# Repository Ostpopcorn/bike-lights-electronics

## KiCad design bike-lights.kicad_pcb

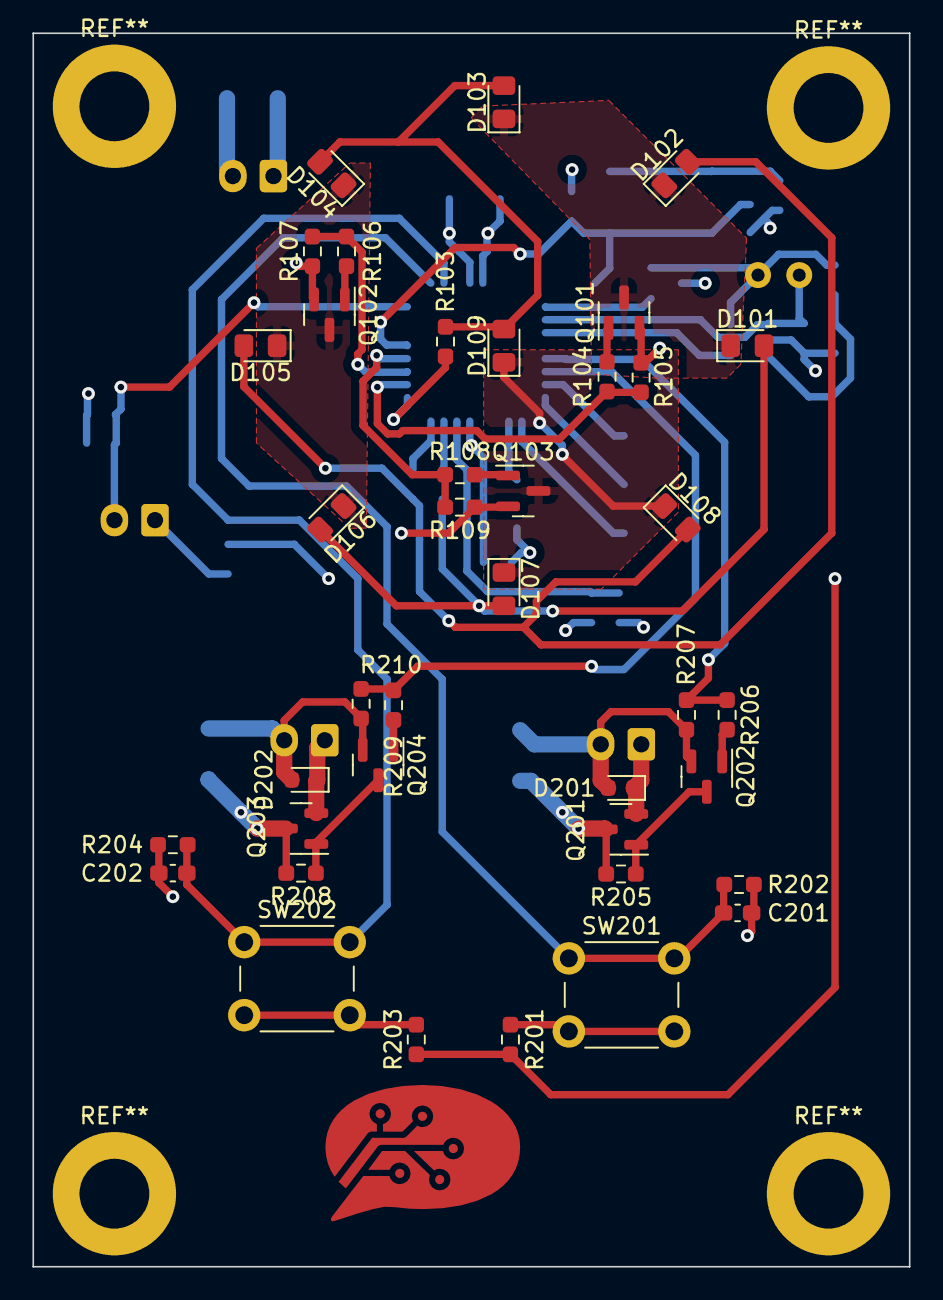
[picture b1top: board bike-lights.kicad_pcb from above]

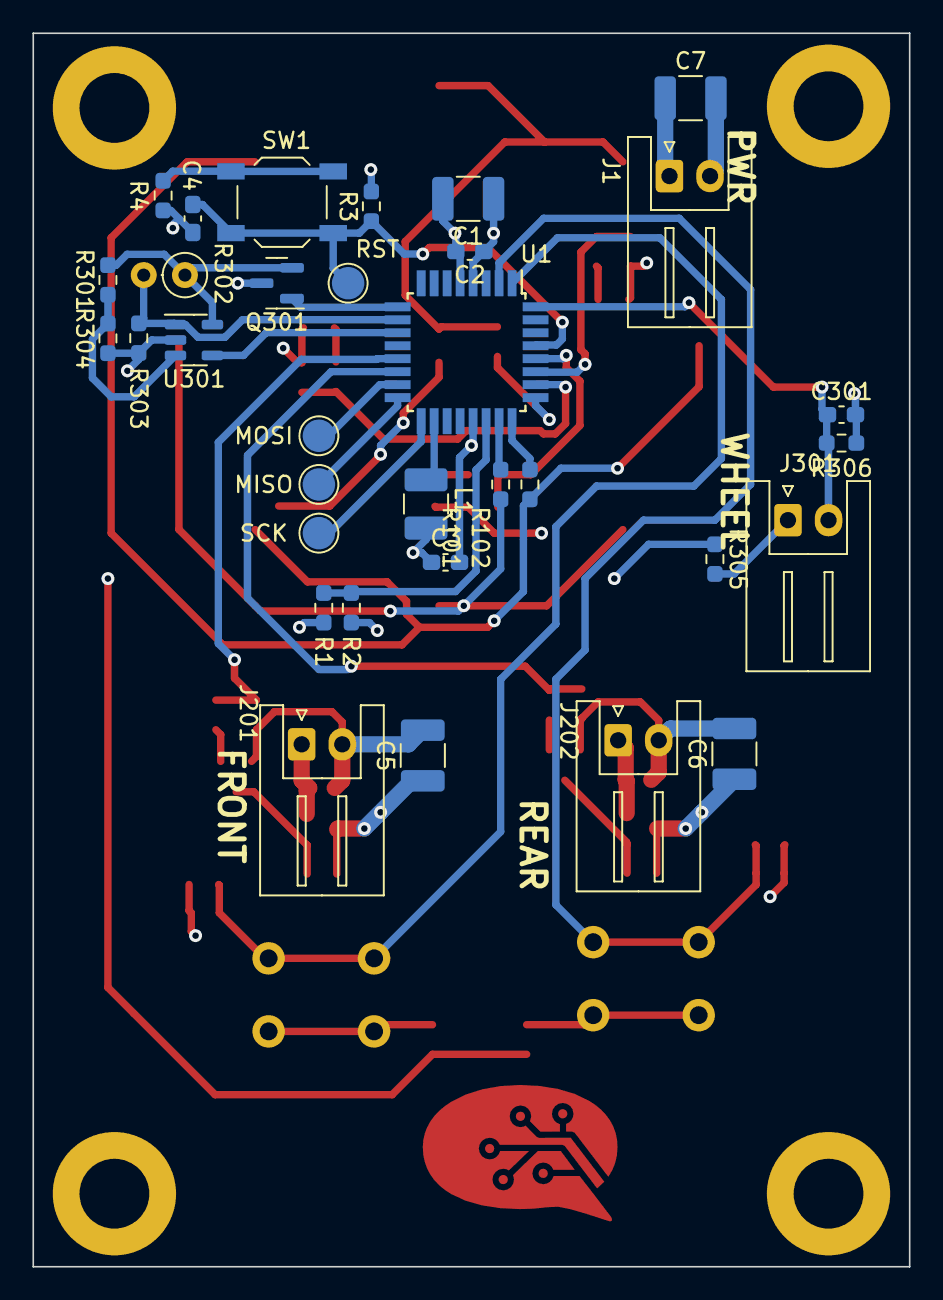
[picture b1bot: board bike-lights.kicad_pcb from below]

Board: 4 copper layers, 54.0 x 76.0 mm, 73 parts (33 on the bottom side), 44 nets.

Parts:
C1, C5, C6, C7: 10uF; C_1210_3225Metric_Pad1.33x2.70mm_HandSolder
C2, C3, C4, C201, C202, C301: 100nF; C_0603_1608Metric_Pad1.08x0.95mm_HandSolder
D101, D102, D103, D104, D105, D106, D107, D108, D109: LED_Small; LED_0805_2012Metric_Pad1.15x1.40mm_HandSolder
D201, D202: D; D_0603_1608Metric
J1: Conn_01x02_Female; JST_XH_S2B-XH-A_1x02_P2.50mm_Horizontal
J201, J202, J301: Conn_01x02_Male; JST_XH_S2B-XH-A_1x02_P2.50mm_Horizontal
L1: L; L_1210_3225Metric_Pad1.42x2.65mm_HandSolder
MISO: TestPoint_Pad_D2.0mm
MOSI: TestPoint_Pad_D2.0mm
Q101, Q102, Q103, Q202, Q204: BST82-1; SOT-23
Q201, Q203, Q301: A1SHB; SOT-23
R1, R2, R105, R107, R207, R210, R301, R304: 100k; R_0603_1608Metric_Pad0.98x0.95mm_HandSolder
R3, R109, R303: 10k; R_0603_1608Metric_Pad0.98x0.95mm_HandSolder
R4, R201, R203, R305: 10R; R_0603_1608Metric_Pad0.98x0.95mm_HandSolder
R101, R102, R103: R; R_0603_1608Metric_Pad0.98x0.95mm_HandSolder
R104, R106, R108, R206, R209: R100; R_0603_1608Metric_Pad0.98x0.95mm_HandSolder
R202, R204, R306: 10K; R_0603_1608Metric_Pad0.98x0.95mm_HandSolder
R205, R208: 1k; R_0603_1608Metric_Pad0.98x0.95mm_HandSolder
R302: R_Photo; R_Axial_DIN0207_L6.3mm_D2.5mm_P2.54mm_Vertical
RST: TestPoint_Pad_D2.0mm
SCK: TestPoint_Pad_D2.0mm
SW1: SW_Push; SW_SPST_TL3342
SW201, SW202: SW_Push; SW_PUSH_6mm_H5mm
U1: ATtiny48-A; TQFP-32_7x7mm_P0.8mm
U301: LM397; SOT-23-5
ost-bubble_12mm_Copper: G***; ost-bubble_12mm_Copper

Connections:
+3V3: C1.1, C2.1, C3.1, L1.1, Q301.3 (D), R3.2, R201.1, R203.1, R305.1, U1.4 (VCC)
/3V3PHOTO: Q301.2 (S), R301.2, R302.1, U301.5 (V+)
/BTN1: C201.1, R202.1, SW201.1, U1.1 (PD3)
/BTN2: C202.1, R204.1, SW202.1, U1.2 (PD4)
/ENABLEPHOTO: Q301.1 (G), U1.9 (PD5)
/LEDA1: R101.2, U1.23 (PC0)
/LEDA1INT: D101.2 (A), D106.2 (A), D107.2 (A), R101.1
/LEDA2: R102.2, U1.24 (PC1)
/LEDA2INT: D102.2 (A), D105.2 (A), D108.2 (A), R102.1
/LEDA3: R103.2, U1.25 (PC2)
/LEDA3INT: D103.2 (A), D104.2 (A), D109.2 (A), R103.1
/LEDC1: R104.2, R105.1, U1.26 (PC3)
/LEDC2: R106.2, R107.2, U1.27 (PC4)
/LEDC3: R108.1, R109.2, U1.28 (PC5)
/LIGHTF: R206.1, R207.2, U1.13 (PB1)
/LIGHTR: R209.1, R210.2, U1.14 (PB2)
/MISO: MISO.1, U1.16 (PB4)
/MOSI: MOSI.1, U1.15 (PB3)
/PHOTO: R302.2, R303.2, U1.10 (PD6), U301.1 (-)
/PHOTOCOMP: U1.11 (PD7), U301.4
/RESET: C4.1, R3.1, RST.1, SW1.1, U1.29 (~RESET/PC6)
/SCK: SCK.1, U1.17 (PB5)
/VSENSE: R1.1, R2.2, U1.22 (PA1)
/WHEEL: C301.1, J301.2, R306.1, U1.32 (PD2)
GND: C1.2, C2.2, C3.2, C4.2, C5.2, C6.2, C7.2, C201.2, C202.2, C301.2, D201.2 (A), D202.2 (A), J1.2, J201.2, J202.2, Q101.2 (S), Q102.2 (S), Q103.2 (S), Q202.2 (S), Q204.2 (S), R2.1, R4.2, R105.2, R107.1, R109.1, R202.2, R204.2, R207.1, R210.1, R303.1, R304.1, R306.2, U1.5 (GND), U1.21 (GND), U301.2 (V-)
unnamed: D101.1 (K), D102.1 (K), D103.1 (K), Q101.3 (D)
unnamed: D104.1 (K), D105.1 (K), D106.1 (K), Q102.3 (D)
unnamed: D107.1 (K), D108.1 (K), D109.1 (K), Q103.3 (D)
unnamed: D201.1 (K), J201.1, Q201.2 (S)
unnamed: D202.1 (K), J202.1, Q203.2 (S)
unnamed: J301.1, R305.2
unnamed: L1.2, U1.18 (AVCC)
unnamed: Q101.1 (G), R104.1
unnamed: Q102.1 (G), R106.1
unnamed: Q103.1 (G), R108.2
unnamed: Q201.1 (G), Q202.3 (D), R205.1
unnamed: Q202.1 (G), R206.2
unnamed: Q203.1 (G), Q204.3 (D), R208.1
unnamed: Q204.1 (G), R209.2
unnamed: R4.1, SW1.2
unnamed: R201.2, SW201.2
unnamed: R203.2, SW202.2
unnamed: R301.1, R304.2, U301.3 (+)
VCC: C5.1, C6.1, C7.1, J1.1, Q201.3 (D), Q203.3 (D), R1.2, R205.2, R208.2

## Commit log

2021-10-30 Added empty KiCad project. Added SymbolOST lib as submodule.
2021-10-30 Added submodule the propper way.
2021-10-31 Added correct repo as submodule.
2022-07-18 Did most of the layout. Added Light sensor (LDR) and wheel sensor to the board.
